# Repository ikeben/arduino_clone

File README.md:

# arduino_clone#

arduino clone desined with kicad 6
*Not perfect yet

https://github.com/ikeben/arduino_clone/blob/master/3dv.png

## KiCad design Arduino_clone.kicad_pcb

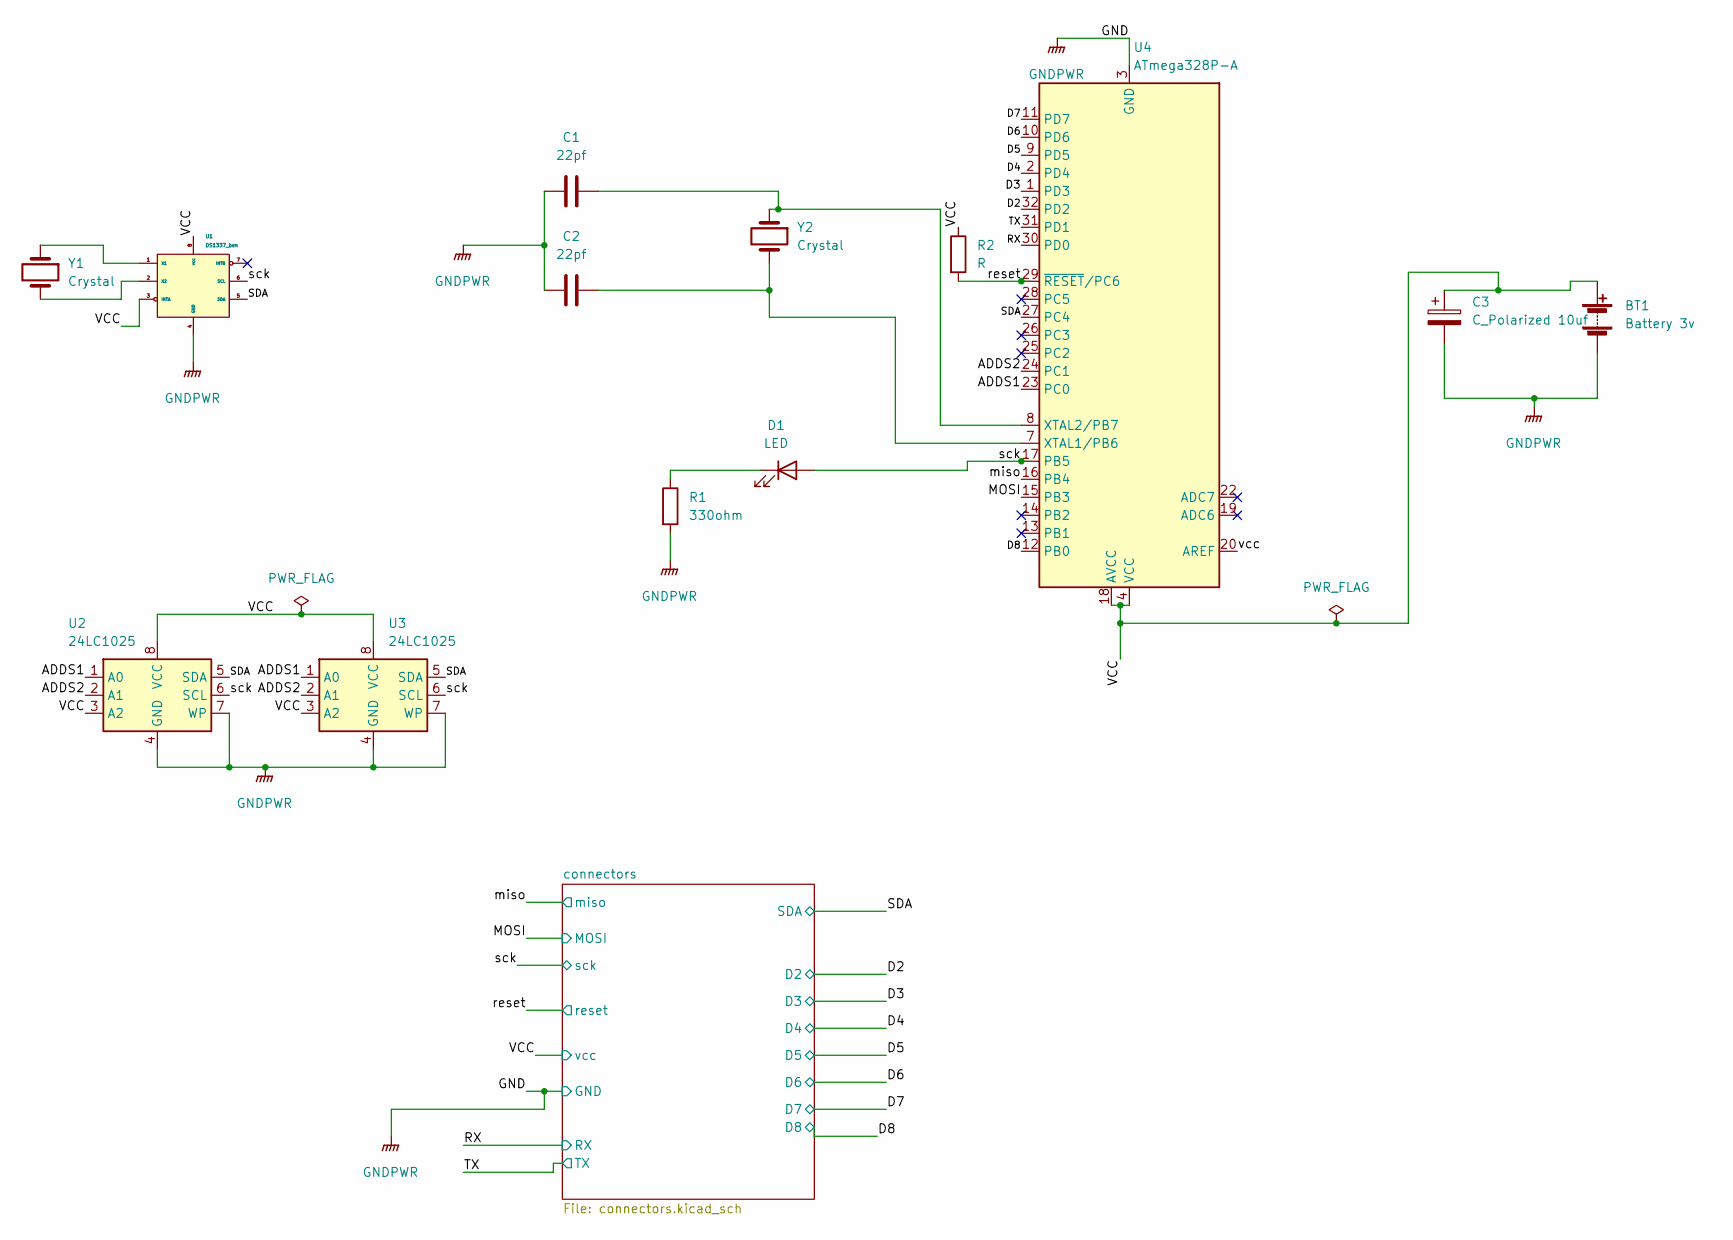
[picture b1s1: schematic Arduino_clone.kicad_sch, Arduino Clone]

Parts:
BT1: Battery 3v; PinSocket_1x02_P2.54mm_Vertical
C1, C2: 22pf; C_0805_2012Metric_Pad1.18x1.45mm_HandSolder
C3: C_Polarized 10uf; C_0805_2012Metric_Pad1.18x1.45mm_HandSolder
D1: LED; LED_0805_2012Metric_Pad1.15x1.40mm_HandSolder
R1: 330ohm; R_0805_2012Metric_Pad1.20x1.40mm_HandSolder
R2: R; R_0805_2012Metric_Pad1.20x1.40mm_HandSolder
U1: DS1337_ben; SO-8_5.3x6.2mm_P1.27mm
U2, U3: 24LC1025; SOP-8_5.28x5.23mm_P1.27mm
U4: ATmega328P-A; TQFP-32_7x7mm_P0.8mm
Y1, Y2: Crystal; Crystal_SMD_MicroCrystal_CC7V-T1A-2Pin_3.2x1.5mm_HandSolder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

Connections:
/ADDS1: U2.1 (A0), U3.1 (A0), U4.23 (PC0)
/ADDS2: U2.2 (A1), U3.2 (A1), U4.24 (PC1)
/D2: U4.32 (PD2); also elsewhere on the board
/D3: U4.1 (PD3); also elsewhere on the board
/D4: U4.2 (PD4); also elsewhere on the board
/D5: U4.9 (PD5); also elsewhere on the board
/D6: U4.10 (PD6); also elsewhere on the board
/D7: U4.11 (PD7); also elsewhere on the board
/D8: U4.12 (PB0); also elsewhere on the board
/MOSI: U4.15 (PB3); also elsewhere on the board
/RX: U4.30 (PD0); also elsewhere on the board
/SDA: U1.5 (SDA), U2.5 (SDA), U3.5 (SDA), U4.27 (PC4); also elsewhere on the board
/TX: U4.31 (PD1); also elsewhere on the board
/VCC: BT1.1 (+), C3.1, R2.1, U1.3 (INTA), U1.8 (vcc), U2.3 (A2), U2.8 (VCC), U3.3 (A2), U3.8 (VCC), U4.4 (VCC), U4.6 (VCC), U4.18 (AVCC); also elsewhere on the board
/miso: U4.16 (PB4); also elsewhere on the board
/reset: R2.2, U4.29 (~RESET/PC6); also elsewhere on the board
/sck: D1.2 (A), U1.6 (SCL), U2.6 (SCL), U3.6 (SCL), U4.17 (PB5); also elsewhere on the board
/vcc: U4.20 (AREF)
GNDPWR: BT1.2 (-), C1.1, C2.1, C3.2, R1.2, U1.4 (GND), U2.4 (GND), U2.7 (WP), U3.4 (GND), U3.7 (WP), U4.3 (GND), U4.5 (GND), U4.21 (GND); also elsewhere on the board
unnamed: C1.2, U4.8 (XTAL2/PB7), Y2.1
unnamed: C2.2, U4.7 (XTAL1/PB6), Y2.2
unnamed: D1.1 (K), R1.1
unnamed: U1.1 (X1), Y1.1
unnamed: U1.2 (X2), Y1.2

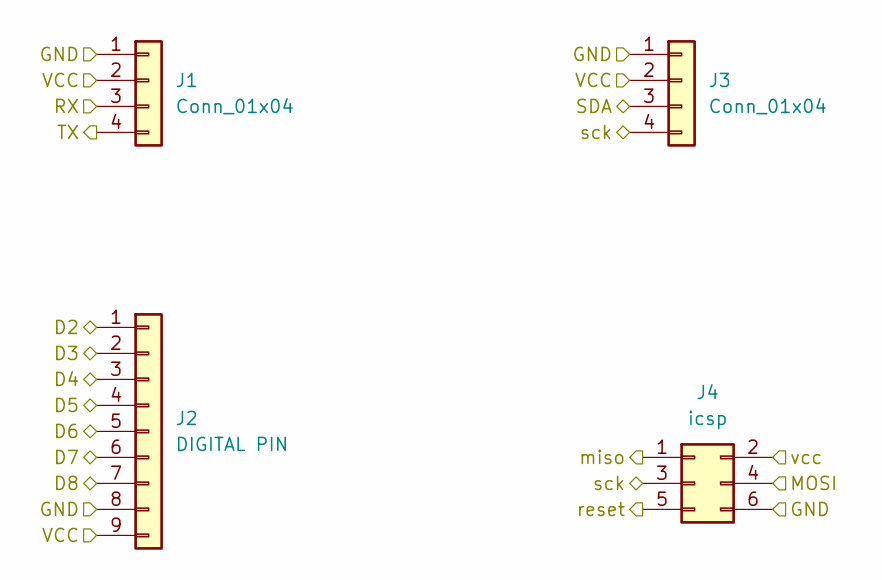
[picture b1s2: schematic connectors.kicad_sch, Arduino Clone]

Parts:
J1, J3: Conn_01x04; PinSocket_1x04_P2.54mm_Vertical
J2: DIGITAL PIN; PinSocket_1x09_P2.54mm_Vertical
J4: icsp; PinSocket_2x03_P2.54mm_Vertical

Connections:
/D2: J2.1; also elsewhere on the board
/D3: J2.2; also elsewhere on the board
/D4: J2.3; also elsewhere on the board
/D5: J2.4; also elsewhere on the board
/D6: J2.5; also elsewhere on the board
/D7: J2.6; also elsewhere on the board
/D8: J2.7; also elsewhere on the board
/MOSI: J4.4; also elsewhere on the board
/RX: J1.3; also elsewhere on the board
/SDA: J3.3; also elsewhere on the board
/TX: J1.4; also elsewhere on the board
/VCC: J4.2; also elsewhere on the board
/connectors/VCC: J1.2, J2.9, J3.2
/miso: J4.1; also elsewhere on the board
/reset: J4.5; also elsewhere on the board
/sck: J3.4, J4.3; also elsewhere on the board
GNDPWR: J1.1, J2.8, J3.1, J4.6; also elsewhere on the board

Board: 2 copper layers, 17 parts (0 on the bottom side), 24 nets, no tracks yet.

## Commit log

2022-09-12 eeschema page setup
2022-09-12 setup title block
2022-09-19 added
2022-09-19 creating a new symbol for the clock
2022-09-19 annotate symbol
2022-09-21 added heirechy sheets and linked the component in eeschema
2022-09-21 connceting wires together before DRC
2022-10-03 set design rules and loaded component for pcb new
2022-10-03 layout on pcbnew
2022-10-04 created outline and mounting holes
2022-10-04 fully routed boared in 2 layers
2022-10-04 copper fillxone on the 2layer boared
2022-10-04 complete work on 2 layer boared added silkscreen
2022-10-04 added pcbnew of the boared
